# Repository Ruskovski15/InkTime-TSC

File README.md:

# InkTime

Open-source smartwatch hardware platform built around the **Nordic nRF52840**. The project integrates a **1.54" e-paper display**, **3-axis IMU**, **battery charger**, **fuel gauge**, **haptic feedback driver**, **USB-C connectivity**, and a compact Li-Po-powered form factor designed to fit the provided InkTime enclosure.

This repository contains the complete hardware design package for the InkTime board:
- native Fusion Electronics files (`.sch`, `.brd`)
- schematic PDF export
- manufacturing outputs (Gerbers, BOM, Pick and Place)
- 3D mechanical assembly (`.f3z`)
- PCB and assembly images

---

Quick links:
- [Schematic source](Hardware/SCHEMATIC.sch)
- [Board source](Hardware/PCB.brd)
- [Schematic PDF](Hardware/Schematic.pdf)
- [Manufacturing BOM](Manufacturing/BOM.xlsx)
- [Pick and Place](Manufacturing/PickAndPlace.mnt)
- [Gerbers](Manufacturing/Gerbers.zip)
- [Mechanical assembly](Mechanical/Electronics%20Design%20InkTime.f3z)

---

## PCB renders

### 3D PCB view

### Top layer

### Bottom layer

### Schematic overview

---

## Block diagram

```mermaid
flowchart LR
    USB[USB-C]
    BAT["Li-Po Battery<br/>3.7V / 250mAh"]
    CHG["BQ25180<br/>Charger + Power Path"]
    REG["RT6160A<br/>Buck-Boost 3.3V"]
    MCU["nRF52840<br/>BLE MCU"]
    IMU["BMA423<br/>3-axis accelerometer"]
    FG["MAX17048<br/>Fuel gauge"]
    HAP["DRV2605<br/>Haptic driver"]
    MOTOR[Vibration motor]
    EPDPWR["EPD drive circuit<br/>boost / analog rails"]
    EPD["1.54-inch e-paper display"]
    DBG[SWD test / debug pads]

    USB --> CHG
    BAT --> CHG
    BAT --> FG
    CHG --> REG
    REG --> MCU
    REG --> IMU
    REG --> HAP
    REG --> EPDPWR
    MCU <--> IMU
    MCU <--> FG
    MCU <--> HAP
    HAP --> MOTOR
    MCU --> EPD
    EPDPWR --> EPD
    MCU --> DBG
```

---

## Hardware overview

### 1) Main MCU and wireless subsystem
The central controller is the **nRF52840**, a BLE-capable SoC that handles the smartwatch logic, display updates, USB connectivity, sensor communication, battery monitoring, and haptic control. A **32 MHz high-frequency crystal** is used for the RF subsystem and a **32.768 kHz crystal** is used for low-power timing.

The RF path uses a **Johanson 2.4 GHz chip antenna** matched through a compact network placed near the PCB edge. The board outline includes a dedicated antenna area so the radiating element sits toward the exterior of the device.

### 2) Power architecture
The board is powered from a **single-cell Li-Po battery** and can also be powered/charged from **USB-C VBUS**.

Power is split into two main stages:
1. **BQ25180** handles battery charging, power-path management, and system rail generation.
2. **RT6160A** generates the regulated **3.3 V rail** used by the digital domain.

This separates the battery domain from the regulated logic rail and makes it easier to power the watch both from battery and from USB while charging.

### 3) Display subsystem
The watch uses a **1.54" black/white e-paper display (200x200)** connected through a **24-pin FPC connector**. The MCU communicates with the panel through an SPI-style interface (`CS`, `SCK`, `MOSI`, `DC`, `RST`, `BUSY`).

Because the raw panel requires multiple analog drive voltages, the design also includes a dedicated **e-paper drive circuit** with discrete inductors, MOSFETs, Schottky diodes, and high-voltage capacitors to generate the rails needed by the panel.

### 4) Motion sensing
Motion is provided by a **Bosch BMA423** low-power 3-axis accelerometer. It is connected over **I2C** and exposes **two interrupt lines** to the MCU. This allows the design to support low-power motion-based wakeups, gesture detection, activity recognition, or step-related features.

### 5) Battery monitoring
Battery state-of-charge monitoring is implemented with the **MAX17048** fuel gauge. It is connected to the battery rail and communicates with the MCU over **I2C**, with an additional **ALERT** interrupt line for battery threshold events.

### 6) Haptics
Haptic feedback is driven by a **DRV2605** haptic driver IC. This allows the MCU to trigger vibration effects without driving the motor directly from a GPIO. The driver is paired with a small **coin vibration motor**, which is more suitable for a watch form factor than a large ERM assembly.

### 7) User inputs
The board includes **three buttons**:
- `SW_UP`
- `SW_ENT`
- `SW_DN`

Each button is implemented as an active-low input with an RC network for stable input behavior.

### 8) USB and programming
A **USB-C receptacle** is included for charging and USB connectivity. The data lines are protected with a **USBLC6-2SC6Y** ESD array. Development and flashing are supported through a **Tag-Connect TC2030** debug connector and through several named test pads (`SWDIO`, `SWDCLK`, `SWO`, `RESET`, `3V3`, `GND`, etc.).

---

## Detailed nRF52840 pin usage

The table below summarizes the intended signal allocation of the nRF52840 in this design.

| nRF52840 pin | Signal / function | Connected block | Why this pin is used |
|---|---|---|---|
| `P0.06` | `SDA` | PMIC / IMU / fuel gauge / haptic control bus | Shared I2C data line keeps the peripheral interface compact |
| `P0.07` | `SCL` | PMIC / IMU / fuel gauge / haptic control bus | Shared I2C clock line |
| `P0.11` | `PMIC_INT` | BQ25180 | Interrupt from charger / power-path IC |
| `P0.10` | `ALERT` | MAX17048 | Battery alert / threshold interrupt |
| `P0.08` | `IMU_INT1` | BMA423 | Primary motion interrupt |
| `P1.08` | `IMU_INT2` | BMA423 | Secondary motion interrupt |
| `P0.12` | `HAPTIC_EN` | DRV2605 | Enables haptic driver |
| `P0.13` | `BTN_UP` | `SW_UP` | User input |
| `P0.14` | `BTN_ENTER` | `SW_ENT` | User input |
| `P1.02` | `BTN_DOWN` | `SW_DN` | User input |
| `P0.05` | `EPD_CS` | E-paper display | SPI chip-select for the display |
| `P0.02` | `EPD_SCK` | E-paper display | SPI clock |
| `P0.03` | `EPD_MOSI` | E-paper display | SPI data out to panel |
| `P0.15` | `EPD_DC` | E-paper display | Data/command select |
| `P0.16` | `EPD_RST` | E-paper display | Hardware reset for the panel |
| `P0.17` | `EPD_BUSY` | E-paper display | Busy feedback from the panel |
| `D+` | `USB_D+` | USB-C | Native USB interface of the nRF52840 |
| `D-` | `USB_D-` | USB-C | Native USB interface of the nRF52840 |
| `P0.18/RESET` | `RESET` | Debug / test | Hardware reset access |
| `SWDIO` | `SWDIO` | Tag-Connect + test pad | Programming and debugging |
| `SWDCLK` | `SWDCLK` | Tag-Connect + test pad | Programming and debugging |
| `P1.00` | `SWO` | Test pad | Optional trace / debug output |
| `P0.00`, `P0.01` | `XL1`, `XL2` | 32.768 kHz crystal | Low-power timing reference |

### Notes on the allocation
- The **I2C bus** is shared to minimize pin usage and routing complexity.
- The **display** is placed on a dedicated SPI-style interface because refreshing an e-paper panel is more suitable over a serial display bus than over I2C.
- **USB D+ / D-** are kept on the native USB pins of the nRF52840 to allow direct device connectivity.
- Motion, charging and battery monitoring all expose **interrupts**, which helps reduce polling and improves low-power operation.

---

## BOM summary

A full manufacturing BOM is available in [Manufacturing/BOM.xlsx](Manufacturing/BOM.xlsx). The table below lists the main functional components used in the project.

| Block | Part | Qty. | Role in design | Procurement | Datasheet |
|---|---:|---:|---|---|---|
| MCU + BLE | Nordic **nRF52840-QIAA** | 1 | Main MCU, BLE, USB, sensor/display control | https://www.lcsc.com/product-detail/C190794.html | https://docs.nordicsemi.com/bundle/nRF52840_PS_v1.9/resource/nRF52840_PS_v1.9.pdf |
| Charger / power path | TI **BQ25180** | 1 | Li-Po charger and system power-path management | https://www.ti.com/product/BQ25180 | https://www.ti.com/lit/gpn/BQ25180 |
| 3.3 V regulator | Richtek **RT6160AWSC** | 1 | Buck-boost regulator for the main logic rail | https://www.lcsc.com/product-detail/C7065276.html | https://www.richtek.com/assets/product_file/RT6160A/DS6160A-05.pdf |
| IMU | Bosch **BMA423** | 1 | Motion sensing and interrupts | https://www.lcsc.com/product-detail/C189517.html | https://www.lcsc.com/product-detail/C189517.html |
| Fuel gauge | Maxim / ADI **MAX17048G+T10** | 1 | Battery state-of-charge estimation | https://www.lcsc.com/product-detail/C2682616.html | https://www.analog.com/media/en/technical-documentation/data-sheets/max17048-max17049.pdf |
| Haptic driver | TI **DRV2605YZFR** | 1 | Drives vibration motor with dedicated haptic control | https://www.lcsc.com/product-detail/C81079.html | https://www.ti.com/lit/ds/symlink/drv2605.pdf |
| RF antenna | Johanson **2450AT18B100E** | 1 | 2.4 GHz chip antenna for BLE radio | https://www.lcsc.com/product-detail/C2917717.html | https://www.johansontechnology.com/docs/1187/2450AT18B100_X8XXogU.pdf |
| E-paper panel | Waveshare **WSH-12561 / 1.54" e-paper V2** | 1 | Main low-power display, 200x200, B/W | https://www.tme.eu/en/details/wsh-12561/e-paper/waveshare/12561/ | https://www.tme.eu/Document/0ca57a8ffbcd57b5bca53252eb9d6ec3/WSH-12561.pdf |
| Li-Po battery | Akyga **LP502030 / AKY0106** | 1 | Main energy source, 3.7 V / 250 mAh | https://www.tme.eu/ng/en/details/aky-lp502030/rechargeable-batteries/akyga-battery/aky0106/ | https://www.tme.eu/Document/b9e12bf26ad0ba929a22ab5d58f022cd/AKY0106.pdf |
| Haptic actuator | DFRobot **FIT0774** | 1 | Coin vibration motor | https://www.tme.eu/en/details/df-fit0774/dc-motors/dfrobot/fit0774/ | https://www.tme.eu/en/details/df-fit0774/dc-motors/dfrobot/fit0774/ |
| USB-C connector | kinghelm **KH-TYPE-C-16P** | 1 | Charging + USB interface | https://www.lcsc.com/product-detail/C709357.html | https://datasheet.lcsc.com/lcsc/2404191039_Shenzhen-Kinghelm-Elec-KH-TYPE-C-16P_C709357.pdf |
| E-paper FPC connector | Molex **503480-2400** | 1 | 24-pin display flex connector | https://www.molex.com/en-us/products/part-detail/5034802400 | https://www.molex.com/en-us/products/part-detail/5034802400 |
| ESD protection | ST **USBLC6-2SC6Y** | 1 | Protects VBUS / USB data lines | https://www.st.com/en/protections-and-emi-filters/usblc6-2sc6y.html | https://www.st.com/resource/en/datasheet/usblc6-2sc6y.pdf |
| Debug connector | Tag-Connect **TC2030-IDC** | 1 | Programming and SWD debugging | https://www.tag-connect.com/product/tc2030-idc-nl | https://www.tag-connect.com/wp-content/uploads/bsk-pdf-manager/TC2030-IDC-NL.pdf |
| Passive support network | 0201 / 0402 Rs, Cs, inductors, diodes, MOSFETs | multiple | Decoupling, matching, EPD drive, filters, pull-ups, button conditioning | see [Manufacturing/BOM.xlsx](Manufacturing/BOM.xlsx) | see [Manufacturing/BOM.xlsx](Manufacturing/BOM.xlsx) |

---

## Important design and layout decisions

### Compact watch-oriented form factor
The board outline is constrained by the enclosure and side-button alignment. From the native PCB file, the board fits in an approximately **46 mm × 35 mm** envelope, with additional notches / rounded corners required by the case geometry.

### Top-side component placement
All mounted components are placed on the **TOP layer**, while routing uses both copper layers. This follows the project recommendations and simplifies mechanical integration into the enclosure.

### Antenna placement
The chip antenna is placed at the PCB edge and kept away from large copper regions. This is important for BLE performance and also follows the course constraint that the antenna area should be kept clear.

### Separated power domains
The design separates:
- `VBUS` from USB-C
- `VBAT` from the battery
- regulated digital `3V3`
- dedicated e-paper analog drive rails

This makes the design more robust than powering the entire system directly from the battery rail.

### Testability
Dedicated test pads are provided for:
- battery rail and battery ground
- `3V3`
- `VREG`
- `SDA` / `SCL`
- `SWDIO` / `SWDCLK` / `SWO`
- `RESET`

These pads make bring-up and debugging much easier during EVT.

---

## Mechanical integration

The mechanical archive is available in:
- [Mechanical/Electronics Design InkTime.f3z](Mechanical/Electronics%20Design%20InkTime.f3z)

The design is intended to integrate:
- the PCB
- the Li-Po battery
- the e-paper display
- the vibration motor
- the enclosure

The physical locations of the **USB-C connector**, **display connector**, and **three side buttons** are all important because they are constrained by the enclosure openings and by the display stack-up.

---

## Manufacturing outputs

The repository already includes the standard fabrication outputs:
- [Gerber archive](Manufacturing/Gerbers.zip)
- [Bill of Materials](Manufacturing/BOM.xlsx)
- [Pick and Place](Manufacturing/PickAndPlace.mnt)

This makes the project ready for manufacturing review and assembly export.

---

## Implementation notes / design log

A few implementation aspects were especially important in this project:

1. **The e-paper display is the most demanding peripheral** from a power perspective because it needs more than a simple 3.3 V digital interface; the panel also requires dedicated analog drive rails.
2. **The RF section must be treated carefully** because the nRF52840 antenna matching network and chip antenna performance depend heavily on layout.
3. **Mechanical placement matters as much as the schematic** in a watch design. The USB connector, display FPC, and buttons cannot be placed arbitrarily.
4. **Battery monitoring and charging were intentionally separated from the main regulator** so the system can expose both battery information and a regulated logic rail.
5. **Debug access was preserved** through Tag-Connect and named test pads, which is very useful during bring-up and review.

---

## Files included in this repository

### Hardware
- `Hardware/SCHEMATIC.sch` — editable schematic source
- `Hardware/PCB.brd` — editable PCB source
- `Hardware/Schematic.pdf` — printable schematic export

### Manufacturing
- `Manufacturing/Gerbers.zip` — CAM output for fabrication
- `Manufacturing/BOM.csv`, `Manufacturing/BOM.xlsx` — parts list
- `Manufacturing/PickAndPlace.mnt` — placement export for assembly

### Mechanical
- `Mechanical/Electronics Design InkTime.f3z` — 3D assembly / Fusion archive

### Images
- PCB top / bottom captures
- schematic overview
- 3D PCB render

---

## Author

**Andrei-Alexandru Rusu**

InkTime hardware design repository for the TSC project.

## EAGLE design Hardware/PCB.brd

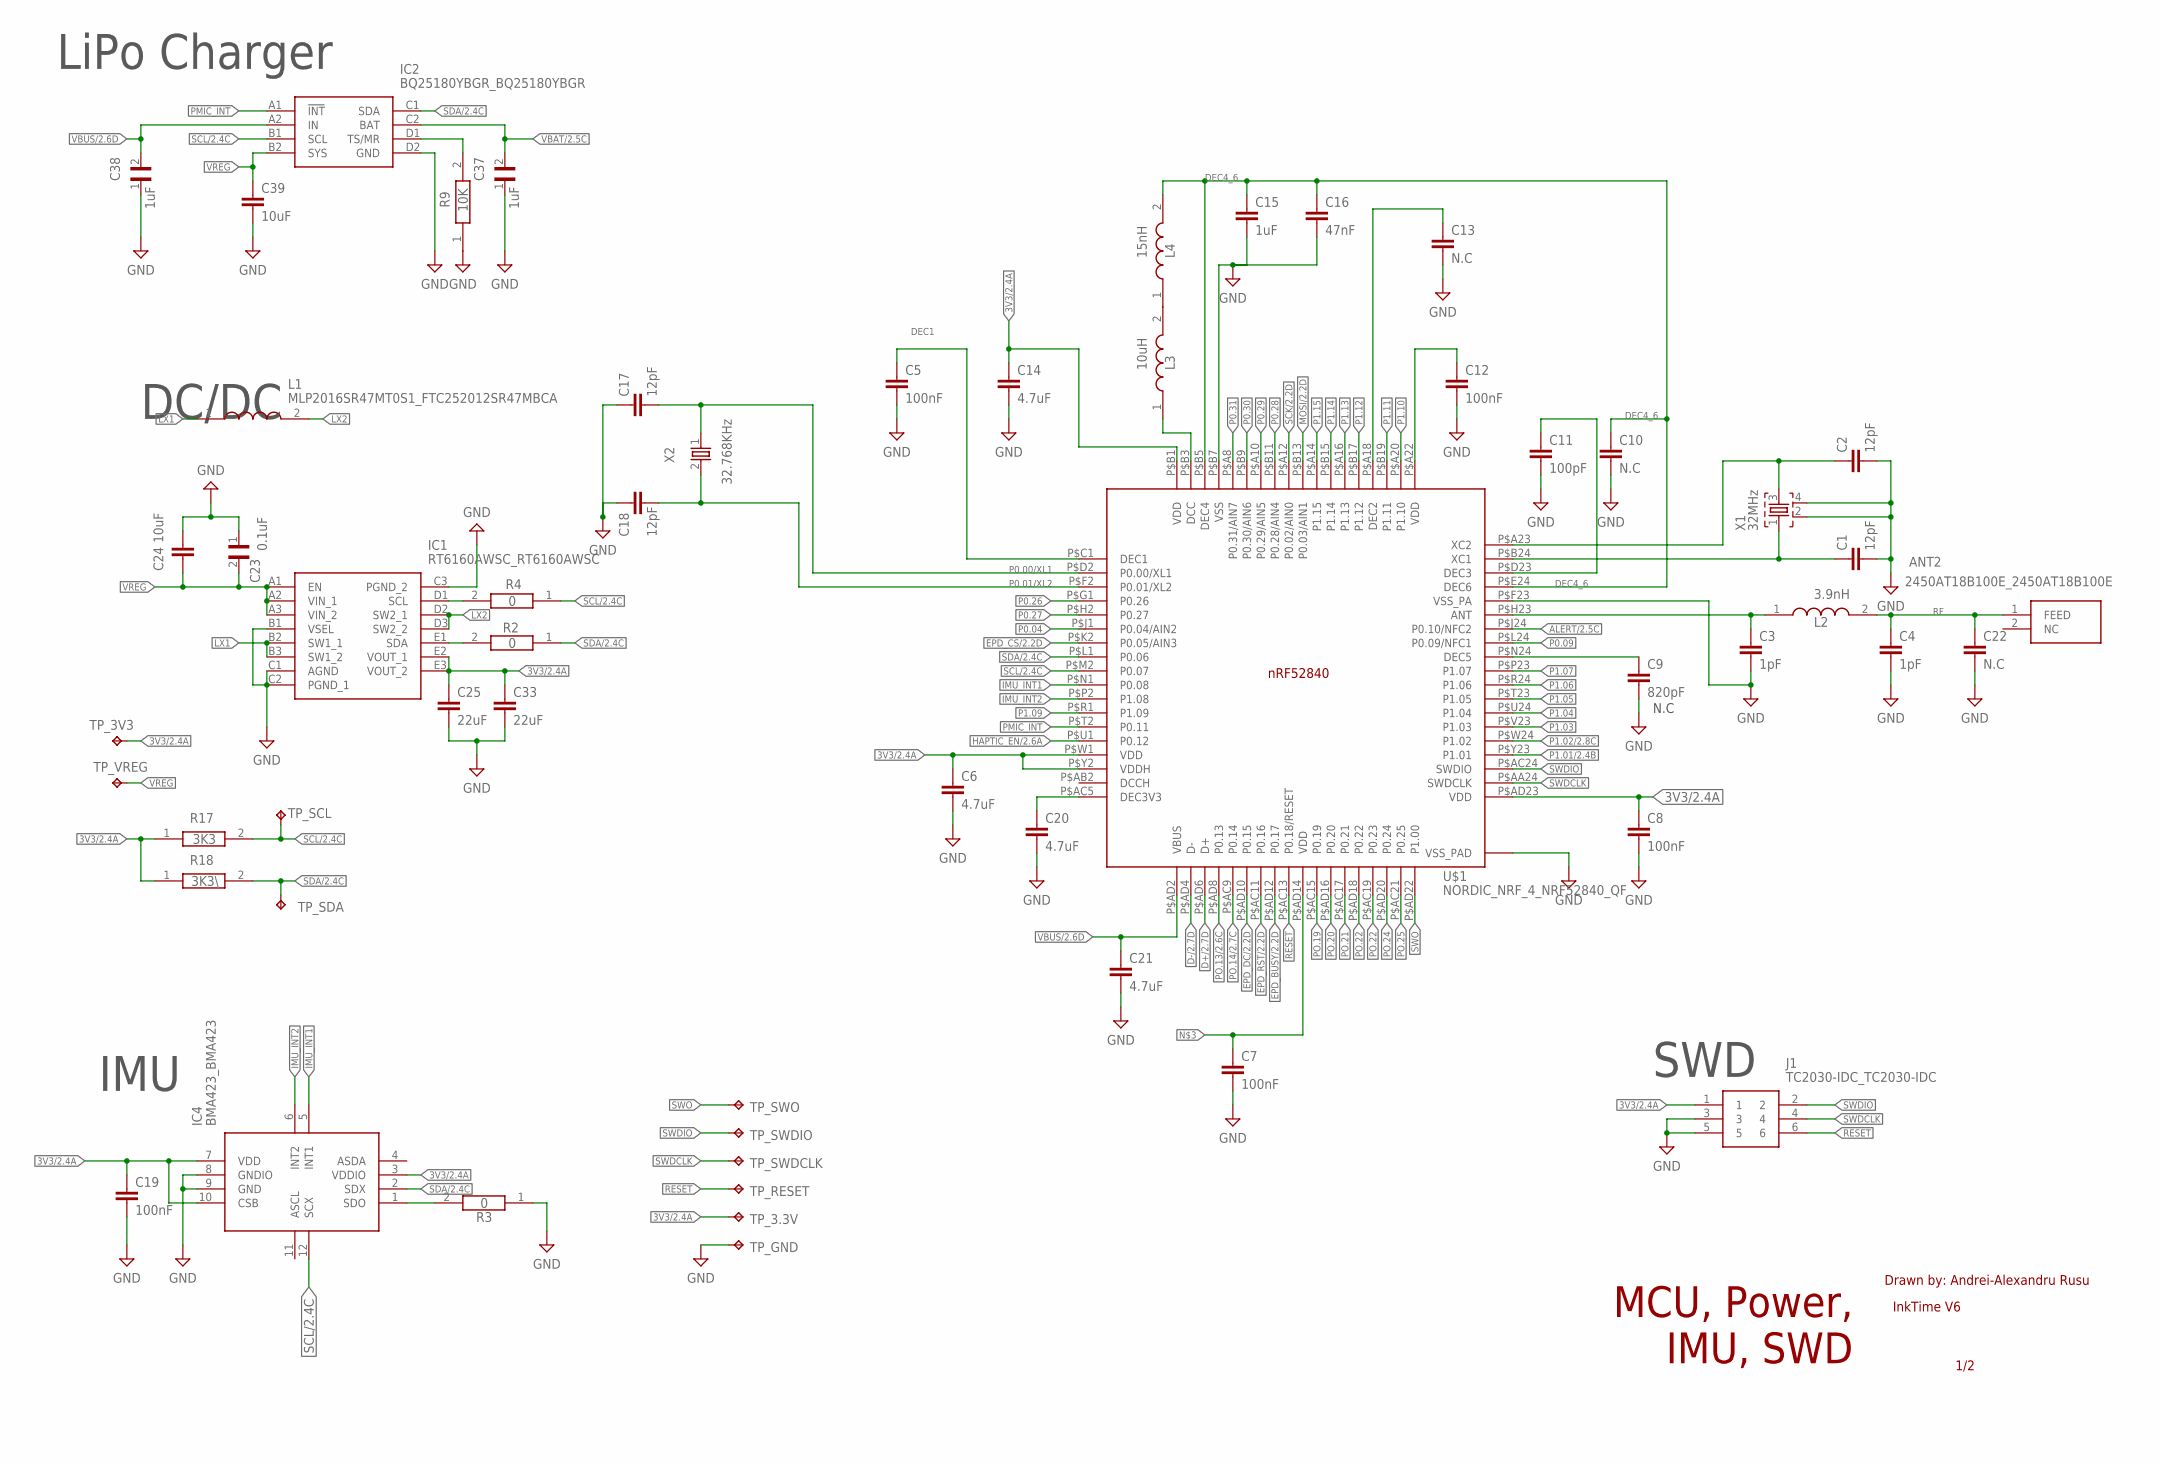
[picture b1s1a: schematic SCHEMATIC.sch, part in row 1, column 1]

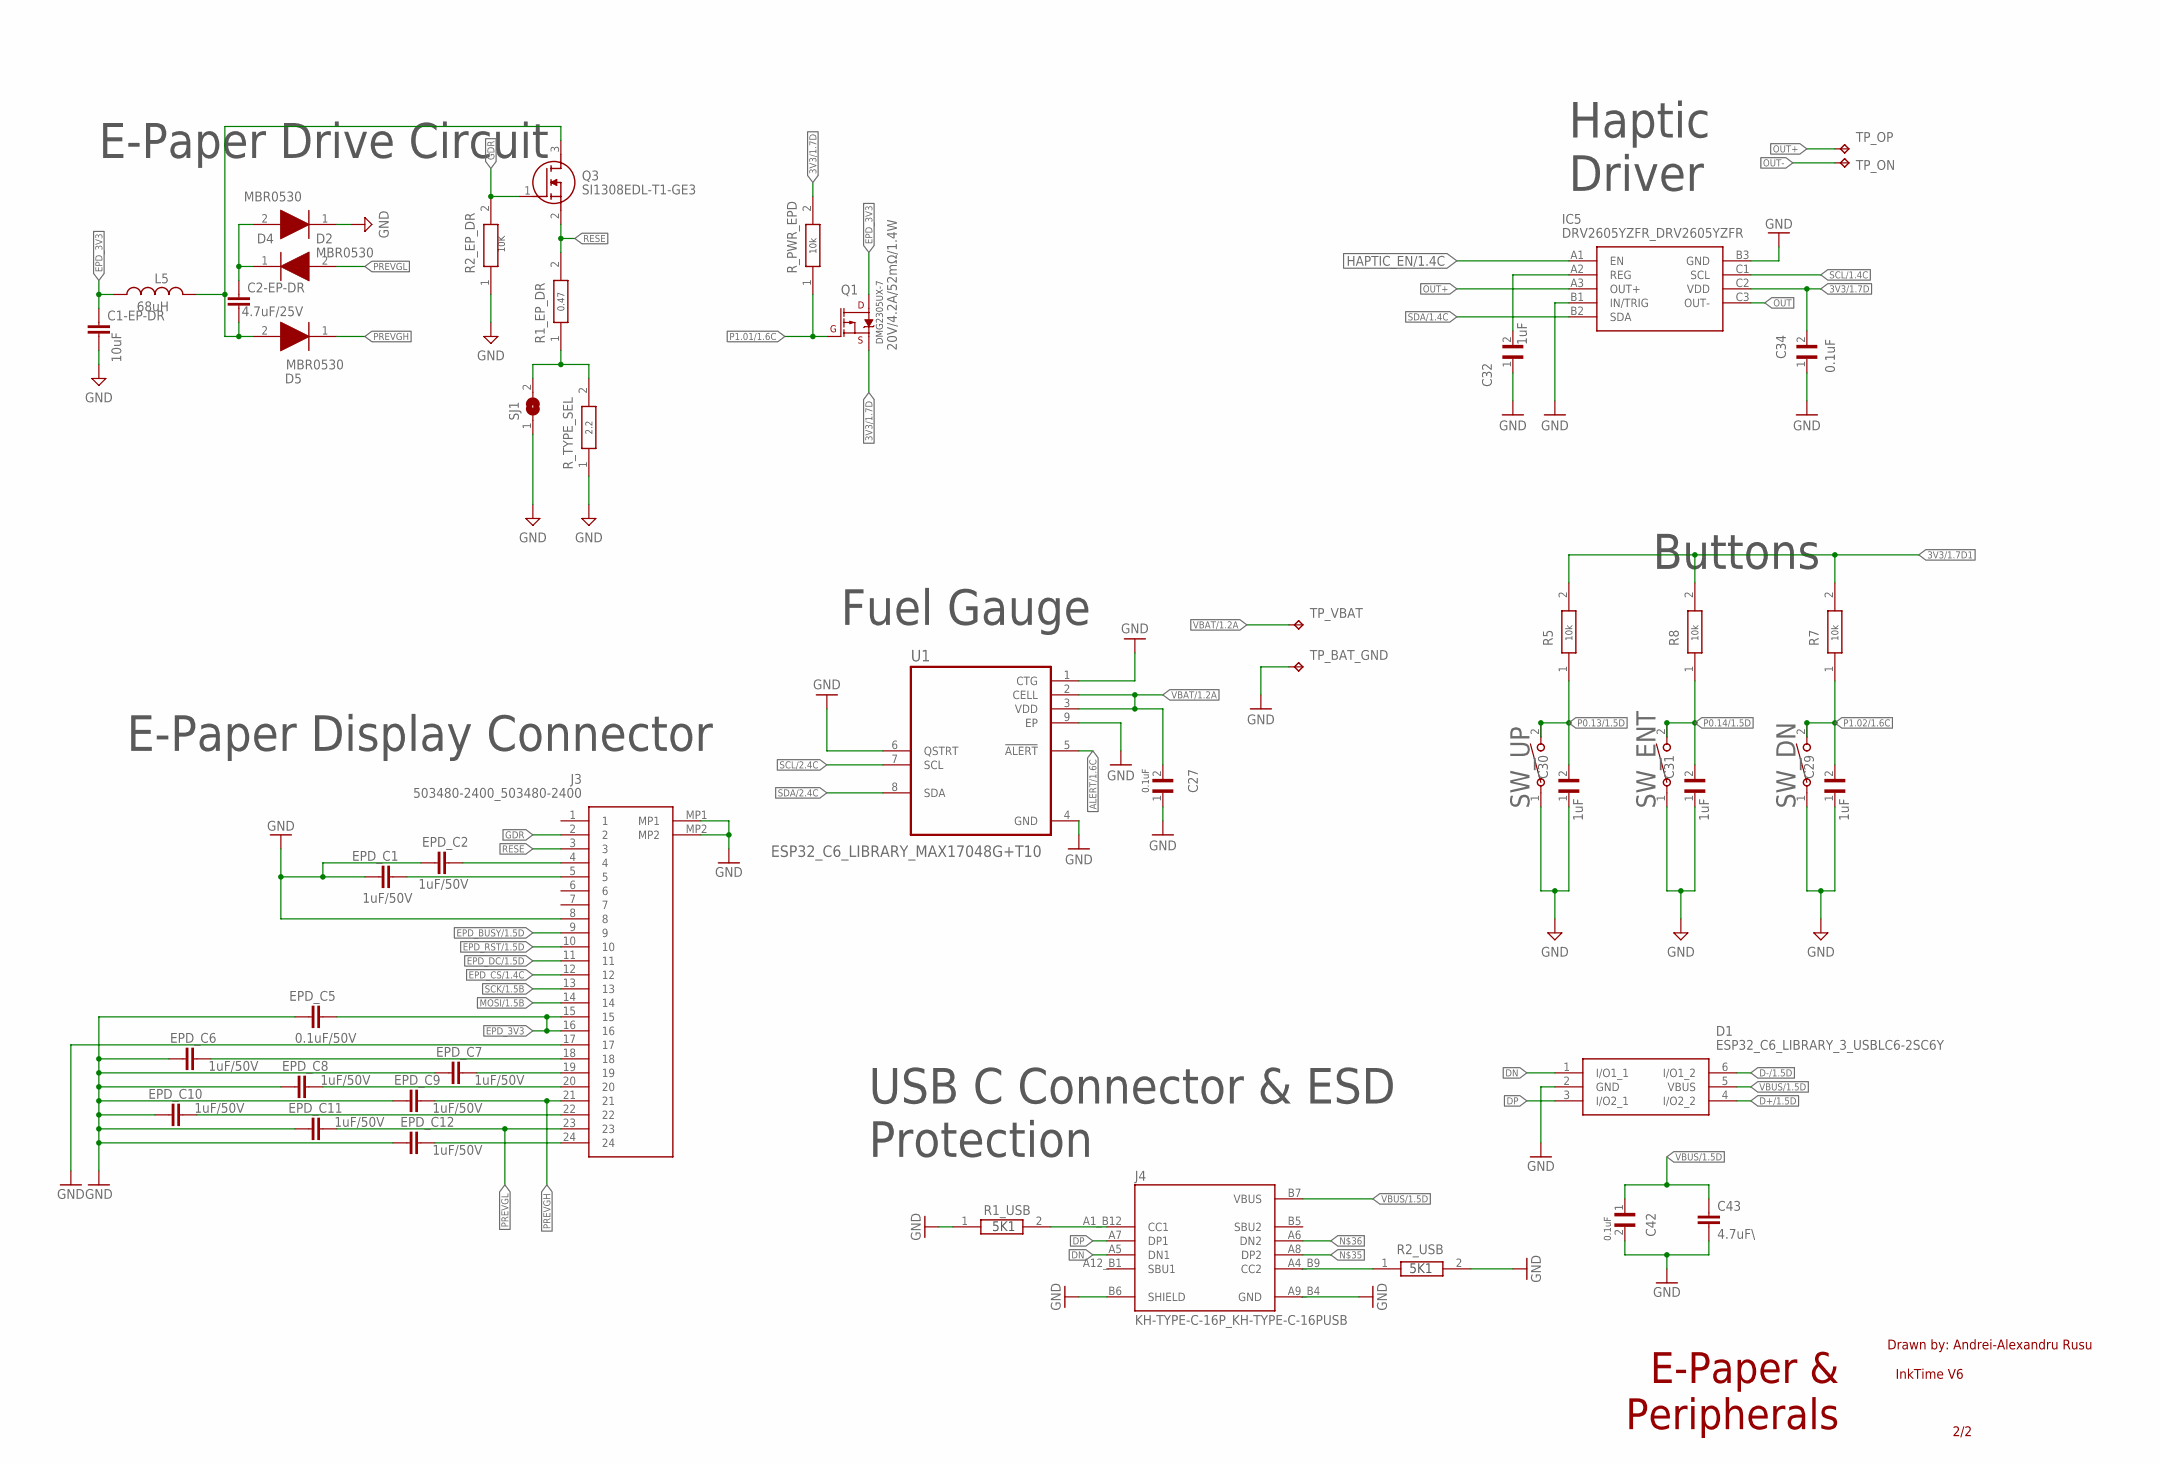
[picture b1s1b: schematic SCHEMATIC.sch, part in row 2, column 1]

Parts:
ANT2: 2450AT18B100E_2450AT18B100E; 2450AT18B100E_ANTC3216X140N
C1, C2, C17, C18: 12pF; NORDIC_NRF_3_RESC0201_L
C1-EP-DR, C24, C39: 10uF; NORDIC_NRF_3_RESC0402_L
C2-EP-DR: 4.7uF/25V; NORDIC_NRF_3_RESC0402_L
C3, C4: 1pF; NORDIC_NRF_3_RESC0201_L
C5, C7, C8, C12, C19: 100nF; NORDIC_NRF_3_RESC0201_L
C6, C14, C20, C21: 4.7uF; NORDIC_NRF_3_RESC0402_L
C9: 820pF; NORDIC_NRF_3_RESC0201_L
C10, C13: N.C; NORDIC_NRF_3_RESC0201_L
C11: 100pF; NORDIC_NRF_3_RESC0201_L
C15: 1uF; NORDIC_NRF_3_RESC0402_L
C16: 47nF; NORDIC_NRF_3_RESC0201_L
C22: N.C; NORDIC_NRF_3_RESC0402_L
C23, C42: 0.1uF; GRM011R60J152KE01L_2_CAPC0201X13N
C25, C33: 22uF; NORDIC_NRF_3_RESC0402_L
C27, C34: 0.1uF; GRM011R60J152KE01L_1_0201
C29, C30, C31, C37, C38: 1uF; GRM011R60J152KE01L_2_CAPC0201X13N
C32: 1uF; GRM011R60J152KE01L_1_0201
C43: 4.7uF\; NORDIC_NRF_3_RESC0402_L
D1: ESP32_C6_LIBRARY_3_USBLC6-2SC6Y; ESP32_C6_LIBRARY_3_SOT95P280X145-6N
D2, D4, D5: MBR0530; ESP32_C6_LIBRARY_5_SOD3716X135N
EPD_C1, EPD_C2, EPD_C6, EPD_C7, EPD_C8, EPD_C9, EPD_C10, EPD_C11, EPD_C12: 1uF/50V; NORDIC_NRF_3_RESC0402_L
EPD_C5: 0.1uF/50V; NORDIC_NRF_3_RESC0201_L
IC1: RT6160AWSC_RT6160AWSC; RT6160AWSC_BGA15C40P3X5_140X230X60
IC2: BQ25180YBGR_BQ25180YBGR; BQ25180YBGR_BGA8C40P2X4_100X155X50
IC4: BMA423_BMA423
IC5: DRV2605YZFR_DRV2605YZFR; DRV2605YZFR_BGA9C50P3X3_144X144X62
J1: TC2030-IDC_TC2030-IDC; TC2030-IDC_TC2030IDC
J3: 503480-2400_503480-2400; 503480-2400_5034802400
J4: KH-TYPE-C-16P_KH-TYPE-C-16PUSB; KH-TYPE-C-16P_KINGHELM_KH-TYPE-C-16P
L1: MLP2016SR47MT0S1_FTC252012SR47MBCA; MLP2016SR47MT0S1_INDC2016X100N
L2: 3.9nH; MLP2016SR47MT0S1_INDC2016X100N
L3: 10uH; MLP2016SR47MT0S1_INDC2016X100N
L4: 15nH; MLP2016SR47MT0S1_INDC2016X100N
L5: 68uH; NORDIC_NRF_2_RESC0402_L
Q1: 20V/4.2A/52mΩ/1.4W; ESP32_C6_LIBRARY_4_ESP32_C6_LIBRARY_4_ESP32_C6_LIBRARY_4_ES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
Q3: SI1308EDL-T1-GE3; ESP32_C6_LIBRARY_6_SOT65P210X110-3N
R1_EP_DR: 0.47; CPF0201D7K68C1_0201
R1_USB, R2_USB: 5K1; CPF0201D7K68C1_0201
R2, R3, R4: 0; CPF0201D7K68C1_0201
R2_EP_DR, R5, R7, R8, R9: 10K; CPF0201D7K68C1_0201
R17: 3K3; CPF0201D7K68C1_0201
R18: 3K3\; CPF0201D7K68C1_0201
R_PWR_EPD: 10K; CPF0201D7K68C1_0201
R_TYPE_SEL: 2.2; CPF0201D7K68C1_0201
SJ1: 0; ESP32_C6_LIBRARY_7_JUMPER_SJ
SW_DN: 2025-10-22_07-23-44_LIBRARY_EVP-AKE31ASW_EVP-AKE3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; 2025-10-22_07-23-44_LIBRARY_SW_EVP-AKE31A_PAN
SW_ENT: 2025-10-22_07-23-44_LIBRARY_EVP-AKE31ASW_EVP-AKE3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; 2025-10-22_07-23-44_LIBRARY_SW_EVP-AKE31A_PAN
SW_UP: 2025-10-22_07-23-44_LIBRARY_EVP-AKE31ASW_EVP-AKE3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; 2025-10-22_07-23-44_LIBRARY_SW_EVP-AKE31A_PAN
TP_3.3V, TP_3V3: HECTOR_WATCH_1_TPTP20R; HECTOR_WATCH_1_TP20R
TP_BAT_GND: HECTOR_WATCH_1_TPTP20R; HECTOR_WATCH_1_TP20R
TP_GND: HECTOR_WATCH_1_TPTP20R; HECTOR_WATCH_1_TP20R
TP_ON: HECTOR_WATCH_1_TPTP20R; HECTOR_WATCH_1_TP20R
TP_OP: HECTOR_WATCH_1_TPTP20R; HECTOR_WATCH_1_TP20R
TP_RESET: HECTOR_WATCH_1_TPTP20R; HECTOR_WATCH_1_TP20R
TP_SCL: HECTOR_WATCH_1_TPTP20R; HECTOR_WATCH_1_TP20R
TP_SDA: HECTOR_WATCH_1_TPTP20R; HECTOR_WATCH_1_TP20R
TP_SWDCLK: HECTOR_WATCH_1_TPTP20R; HECTOR_WATCH_1_TP20R
TP_SWDIO: HECTOR_WATCH_1_TPTP20R; HECTOR_WATCH_1_TP20R
TP_SWO: HECTOR_WATCH_1_TPTP20R; HECTOR_WATCH_1_TP20R
TP_VBAT: HECTOR_WATCH_1_TPTP20R; HECTOR_WATCH_1_TP20R
TP_VREG: HECTOR_WATCH_1_TPTP20R; HECTOR_WATCH_1_TP20R
U1: ESP32_C6_LIBRARY_MAX17048G+T10; ESP32_C6_LIBRARY_SON50P200X200X80-9N
U$1: NORDIC_NRF_4_NRF52840_QF; NORDIC_NRF_4_AQFN50P700X700X85_HS-74N
X1: 32MHz; NORDIC_NRF_BT-XTAL_2016_N
X2: 32.768KHz; NORDIC_NRF_1_XTAL_3215_N

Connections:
3V3/1.7D: C34.2, IC5.C2 (VDD), Q1.2 (S), R_PWR_EPD.2
3V3/1.7D1: R5.2, R7.2, R8.2
3V3/2.4A: C6.1, C8.1, C19.1, C25.1, C33.1, IC1.E2 (VOUT_1), IC1.E3 (VOUT_2), IC4.3 (VDDIO), IC4.7 (VDD), IC4.10 (CSB), J1.1, TP_3.3V.TP, TP_3V3.TP, U$1.P$AD23 (VDD), U$1.P$W1 (VDD), U$1.P$Y2 (VDDH)
ALERT/1.6C: U1.5 (!ALERT)
ALERT/2.5C: U$1.P$J24 (P0.10/NFC2)
D+/1.5D: D1.4 (I/O2_2)
D+/2.7D: U$1.P$AD6 (D+)
D-/1.5D: D1.6 (I/O1_2)
D-/2.7D: U$1.P$AD4 (D-)
DEC1: C5.1, U$1.P$C1 (DEC1)
DEC4_6: C10.1, C15.1, C16.1, L4.2, U$1.P$B5 (DEC4), U$1.P$E24 (DEC6)
DN: D1.1 (I/O1_1), J4.A5 (DN1)
DP: D1.3 (I/O2_1), J4.A7 (DP1)
EPD_3V3: C1-EP-DR.1, EPD_C5.2, J3.15, J3.16, L5.1, Q1.3 (D)
EPD_BUSY/1.5D: J3.9
EPD_BUSY/2.2D: U$1.P$AD12 (P0.17)
EPD_CS/1.4C: J3.12
EPD_CS/2.2D: U$1.P$K2 (P0.05/AIN3)
EPD_DC/1.5D: J3.11
EPD_DC/2.2D: U$1.P$AD10 (P0.15)
EPD_RST/1.5D: J3.10
EPD_RST/2.2D: U$1.P$AC11 (P0.16)
GDR: J3.2, Q3.1 (G), R2_EP_DR.2
GND: C1.2, C1-EP-DR.2, C2.2, C3.2, C4.2, C5.2, C6.2, C7.2, C8.2, C9.2, C10.2, C11.2, C12.2, C13.2, C14.2, C15.2, C16.2, C17.1, C18.1, C19.2, C20.2, C21.2, C22.2, C23.1, C24.1, C25.2, C27.1, C29.1, C30.1, C31.1, C32.1, C33.2, C34.1, C37.1, C38.1, C39.2, C42.2, C43.2, D1.2 (GND), D4.1 (K), EPD_C1.1, EPD_C2.1, EPD_C5.1, EPD_C6.1, EPD_C7.1, EPD_C8.1, EPD_C9.1, EPD_C10.1, EPD_C11.1, EPD_C12.1, IC1.B1 (VSEL), IC1.C1 (AGND), IC1.C2 (PGND_1), IC1.C3 (PGND_2), IC2.D2 (GND), IC4.8 (GNDIO), IC4.9 (GND), IC5.B3 (GND), J1.3, J1.5, J3.8, J3.MP1, J3.MP2, J4.B6 (SHIELD), R1_USB.1, R2_EP_DR.1, R2_USB.2, R3.1, R9.1, R_TYPE_SEL.1, SJ1.1, SW_DN.1, SW_ENT.1, SW_UP.1, TP_BAT_GND.TP, TP_GND.TP, U1.1 (CTG), U1.4 (GND), U1.6 (QSTRT), U1.9 (EP), U$1.P$74 (VSS_PAD), U$1.P$75 (VSS_PAD), U$1.P$76 (VSS_PAD), U$1.P$77 (VSS_PAD), U$1.P$78 (VSS_PAD), U$1.P$79 (VSS_PAD), U$1.P$80 (VSS_PAD), U$1.P$81 (VSS_PAD), U$1.P$82 (VSS_PAD), U$1.P$83 (VSS_PAD), U$1.P$84 (VSS_PAD), U$1.P$85 (VSS_PAD), U$1.P$86 (VSS_PAD), U$1.P$87 (VSS_PAD), U$1.P$88 (VSS_PAD), U$1.P$89 (VSS_PAD), U$1.P$90 (VSS_PAD), U$1.P$B7 (VSS), U$1.P$F23 (VSS_PA), X1.2, X1.4
HAPTIC_EN/1.4C: IC5.A1 (EN)
HAPTIC_EN/2.6A: U$1.P$U1 (P0.12)
IMU_INT1: IC4.5 (INT1), U$1.P$N1 (P0.08)
IMU_INT2: IC4.6 (INT2), U$1.P$P2 (P1.08)
LX1: IC1.B2 (SW1_1), IC1.B3 (SW1_2), L1.1
LX2: IC1.D2 (SW2_1), IC1.D3 (SW2_2), L1.2
MOSI/1.5B: J3.14
MOSI/2.2D: U$1.P$B13 (P0.03/AIN1)
unnamed: C11.1, U$1.P$D23 (DEC3)
unnamed: C3.1, L2.1, U$1.P$H23 (ANT)
unnamed: C7.1, U$1.P$AD14 (VDD)
unnamed: C1.1, U$1.P$B24 (XC1), X1.1
unnamed: C2.1, U$1.P$A23 (XC2), X1.3
unnamed: C20.1, U$1.P$AC5 (DEC3V3)
unnamed: C9.1, U$1.P$N24 (DEC5)
unnamed: C14.1, U$1.P$B1 (VDD)
unnamed: L3.1, U$1.P$B3 (DCC)
unnamed: L3.2, L4.1
unnamed: C13.1, U$1.P$A18 (DEC2)
unnamed: C12.1, U$1.P$A22 (VDD)
unnamed: IC4.1 (SDO), R3.2
unnamed: IC1.D1 (SCL), R4.2
unnamed: IC1.E1 (SDA), R2.2
unnamed: R17.1, R18.1
unnamed: IC2.D1 (TS/MR), R9.2
unnamed: C2-EP-DR.2, D5.2 (A), L5.2, Q3.3 (D)
unnamed: C2-EP-DR.1, D2.1 (K), D4.2 (A)
unnamed: R1_EP_DR.1, R_TYPE_SEL.2, SJ1.2
unnamed: EPD_C2.2, J3.4
unnamed: EPD_C1.2, J3.5
unnamed: EPD_C6.2, J3.18
unnamed: EPD_C7.2, J3.19
unnamed: EPD_C8.2, J3.20
unnamed: EPD_C10.2, J3.22
unnamed: EPD_C12.2, J3.24
unnamed: C32.2, IC5.A2 (REG)
unnamed: J4.A1_B12 (CC1), R1_USB.2
unnamed: J4.A4_B9 (CC2), R2_USB.1
OUT: IC5.C3 (OUT-)
OUT+: IC5.A3 (OUT+), TP_OP.TP
OUT-: TP_ON.TP
P0.00/XL1: C17.2, U$1.P$D2 (P0.00/XL1), X2.1
P0.01/XL2: C18.2, U$1.P$F2 (P0.01/XL2), X2.2
P0.04: U$1.P$J1 (P0.04/AIN2)
P0.09: U$1.P$L24 (P0.09/NFC1)
P0.13/1.5D: C30.2, R5.1, SW_UP.2
P0.14/1.5D: C31.2, R8.1, SW_ENT.2
P0.26: U$1.P$G1 (P0.26)
P0.27: U$1.P$H2 (P0.27)
P0.28: U$1.P$B11 (P0.28/AIN4)
P0.29: U$1.P$A10 (P0.29/AIN5)
P0.30: U$1.P$B9 (P0.30/AIN6)
P0.31: U$1.P$A8 (P0.31/AIN7)
P1.01/1.6C: Q1.1 (G), R_PWR_EPD.1
P1.01/2.4B: U$1.P$Y23 (P1.01)
P1.02/1.6C: C29.2, R7.1, SW_DN.2
P1.02/2.8C: U$1.P$W24 (P1.02)
P1.03: U$1.P$V23 (P1.03)
P1.04: U$1.P$U24 (P1.04)
P1.05: U$1.P$T23 (P1.05)
P1.06: U$1.P$R24 (P1.06)
P1.07: U$1.P$P23 (P1.07)
P1.09: U$1.P$R1 (P1.09)
P1.10: U$1.P$A20 (P1.10)
P1.11: U$1.P$B19 (P1.11)
P1.12: U$1.P$B17 (P1.12)
P1.13: U$1.P$A16 (P1.13)
P1.14: U$1.P$B15 (P1.14)
P1.15: U$1.P$A14 (P1.15)
PMIC_INT: IC2.A1 (!INT), U$1.P$T2 (P0.11)
PO.13/2.6C: U$1.P$AD8 (P0.13)
PO.14/2.7C: U$1.P$AC9 (P0.14)
PO.19: U$1.P$AC15 (P0.19)
PO.20: U$1.P$AD16 (P0.20)
PO.21: U$1.P$AC17 (P0.21)
PO.22: U$1.P$AC19 (P0.23)
PO.24: U$1.P$AD20 (P0.24)
PO.25: U$1.P$AC21 (P0.25)
PREVGH: D5.1 (K), EPD_C9.2, J3.21
PREVGL: D2.2 (A), EPD_C11.2, J3.23
RESE: J3.3, Q3.2 (S), R1_EP_DR.2
RESET: J1.6, TP_RESET.TP, U$1.P$AC13 (P0.18/RESET)
RF: ANT2.1 (FEED), C4.1, C22.1, L2.2
SCK/1.5B: J3.13
SCK/2.2D: U$1.P$A12 (P0.02/AIN0)
SCL/1.4C: IC5.C1 (SCL)
SCL/2.4C: IC2.B1 (SCL), IC4.12 (SCX), R4.1, R17.2, TP_SCL.TP, U1.7 (SCL), U$1.P$M2 (P0.07)
SDA/1.4C: IC5.B2 (SDA)
SDA/2.4C: IC2.C1 (SDA), IC4.2 (SDX), R2.1, R18.2, TP_SDA.TP, U1.8 (SDA), U$1.P$L1 (P0.06)
SWDCLK: J1.4, TP_SWDCLK.TP, U$1.P$AA24 (SWDCLK)
SWDIO: J1.2, TP_SWDIO.TP, U$1.P$AC24 (SWDIO)
SWO: TP_SWO.TP, U$1.P$AD22 (P1.00)
VBAT/1.2A: C27.2, TP_VBAT.TP, U1.2 (CELL), U1.3 (VDD)
VBAT/2.5C: C37.2, IC2.C2 (BAT)
VBUS/1.5D: C42.1, C43.1, D1.5 (VBUS), J4.B7 (VBUS)
VBUS/2.6D: C21.1, C38.2, IC2.A2 (IN), U$1.P$AD2 (VBUS)
VREG: C23.2, C24.2, C39.1, IC1.A1 (EN), IC1.A2 (VIN_1), IC1.A3 (VIN_2), IC2.B2 (SYS), TP_VREG.TP

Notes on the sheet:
LiPo Charger
DC/DC
IMU
SWD
N.C
MCU, Power, IMU, SWD
E-Paper & Peripherals
Drawn by: Andrei-Alexandru Rusu
InkTime V6
1/2
2/2
E-Paper Drive Circuit
0.47
2.2
10K
DMG2305UX-7
10k
Haptic Driver
Fuel Gauge
0.1uF
Buttons
E-Paper Display Connector
5K1
USB C Connector & ESD Protection

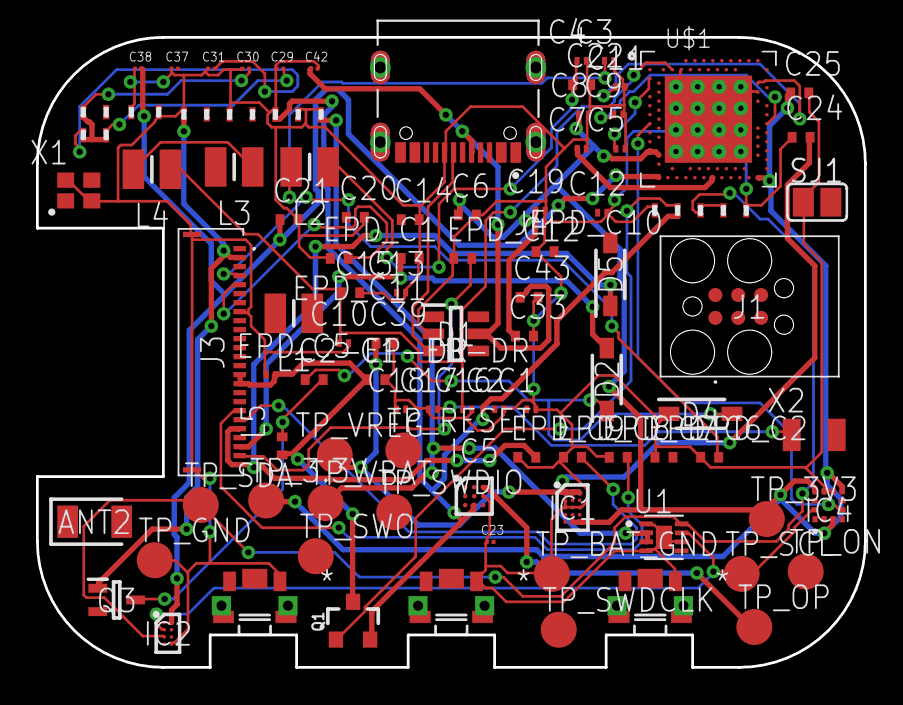
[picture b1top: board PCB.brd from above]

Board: 2 copper layers, 46.0 x 35.0 mm, 105 parts (0 on the bottom side), 67 nets.

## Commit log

2026-04-10 Create Hardware folder
2026-04-10 Add new file Papis
2026-04-10 Add schematic and pcb files
2026-04-10 Delete Hardware/Papis file
    I had to make a folder bro, I was on the website ;((((((
2026-04-10 Add Testing file with initial content
2026-04-10 Create 123
2026-04-10 Prep folders
2026-04-19 Remade Schematic + PCB
    Remade schematic and started on PCB a bit
2026-04-20 Add some of the missing files and edits from PCB and Schematic
    Added some images, edited out the schematic a bit added a 3D model for the USB. Also added Gerbers and BOM
2026-04-20 Trying to push bom and pickandplace
2026-04-20 Add Readme
2026-04-20 Fix readme flowchart

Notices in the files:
parts and their libraries:
COPYRIGHT: Copyright (C) 2025 Ultra Librarian. All rights reserved.
